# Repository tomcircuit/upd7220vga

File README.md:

# upd7220vga
VGA display using NEC uPD7220 Graphic Display Processor and MAX II CPLD

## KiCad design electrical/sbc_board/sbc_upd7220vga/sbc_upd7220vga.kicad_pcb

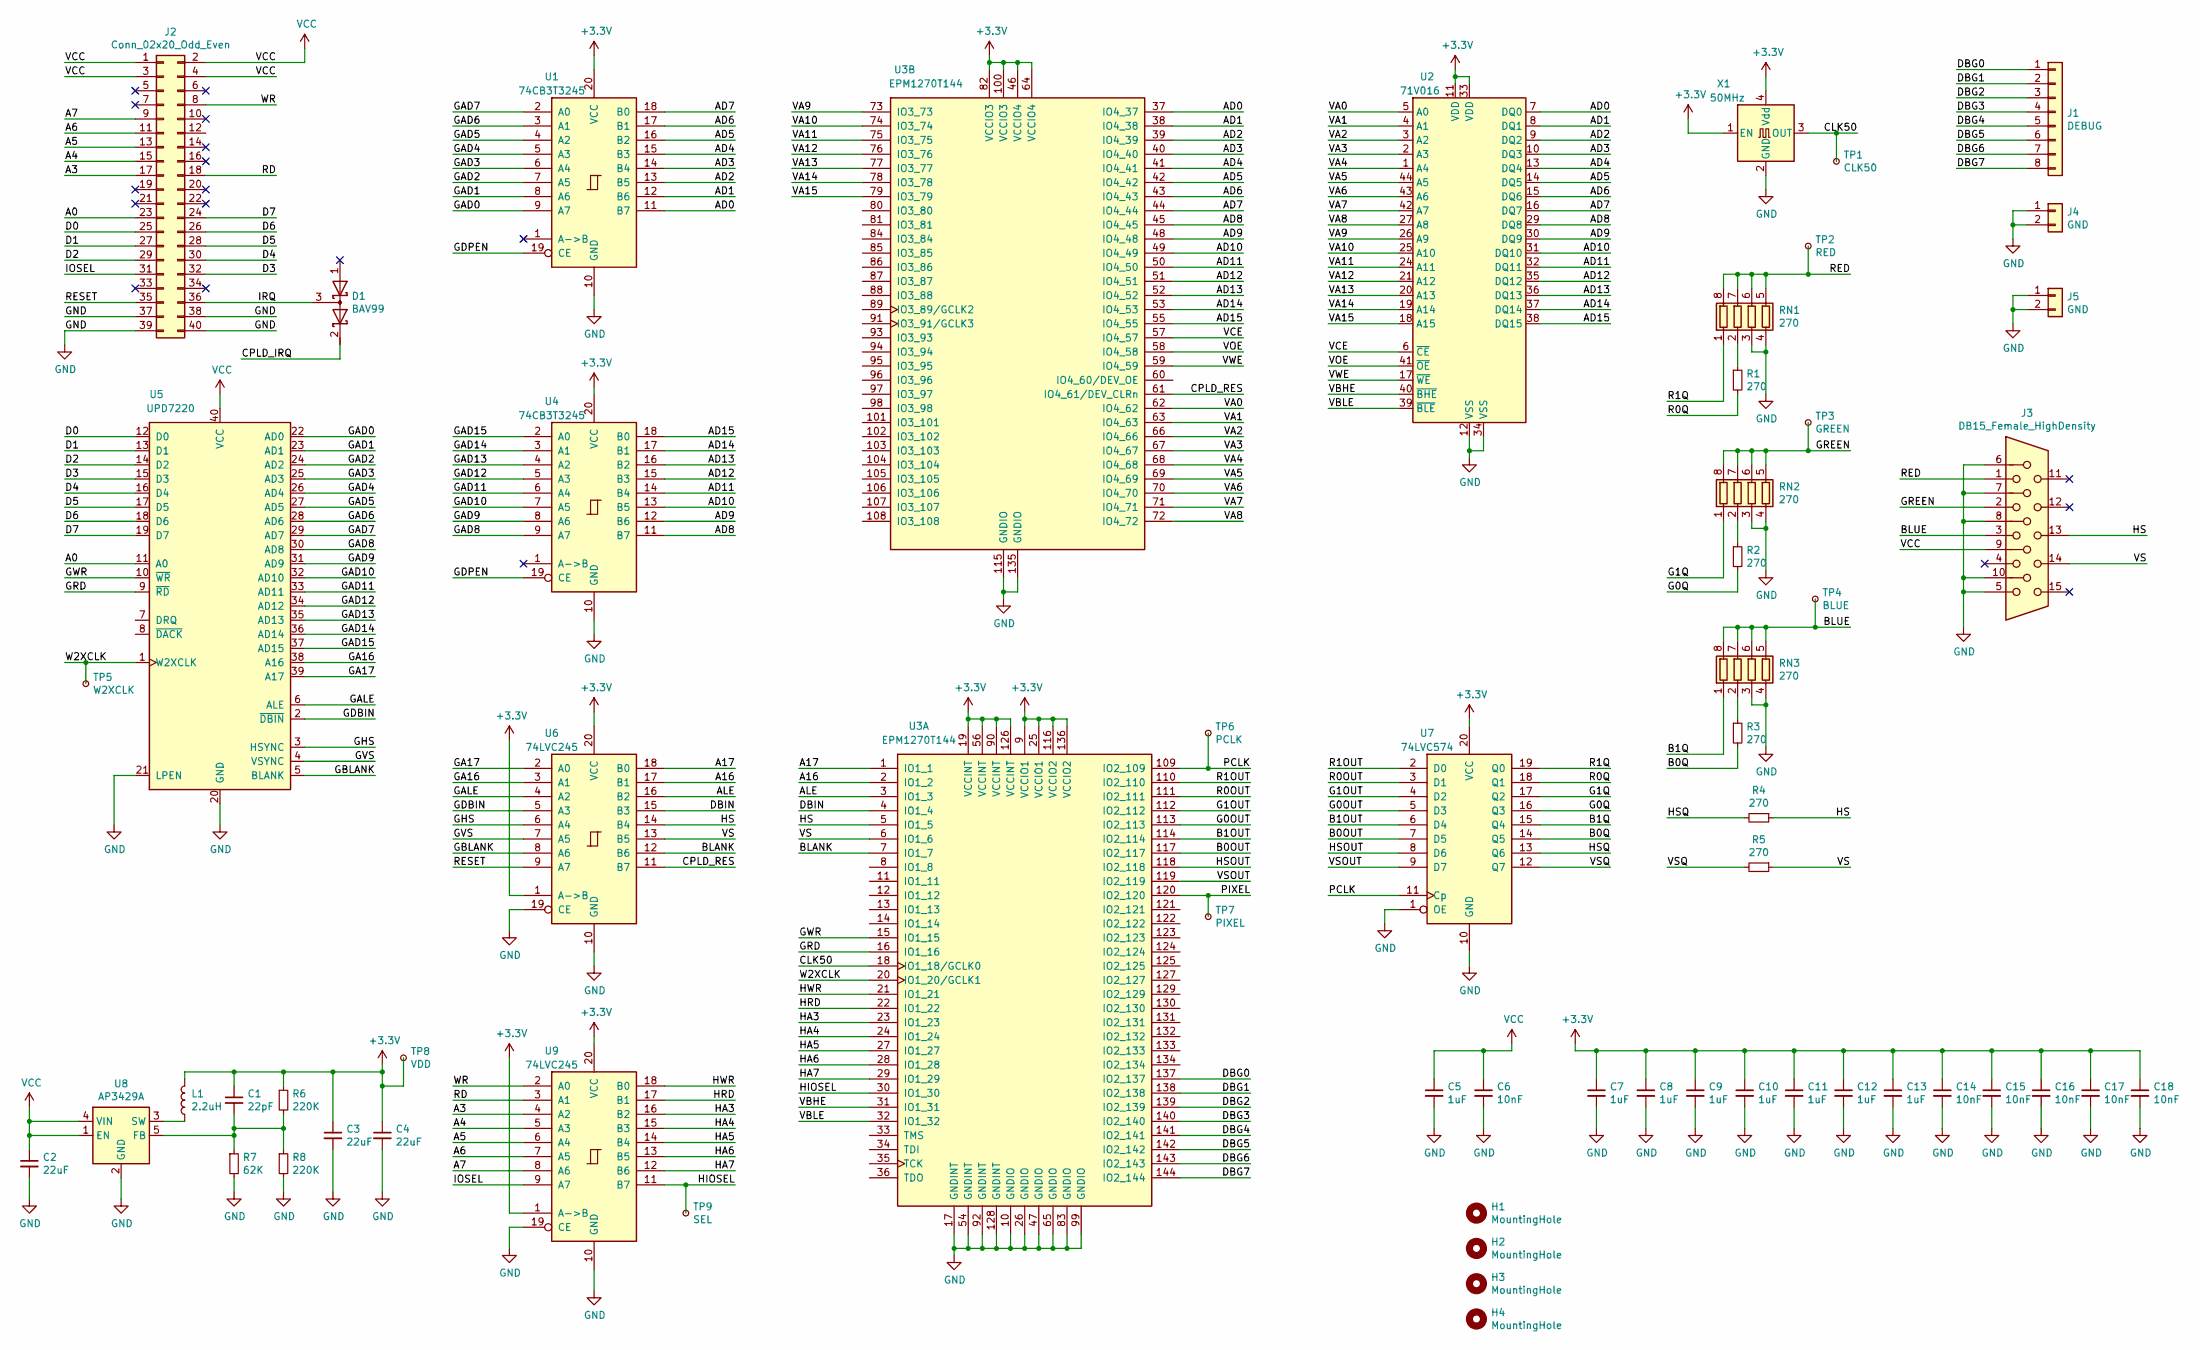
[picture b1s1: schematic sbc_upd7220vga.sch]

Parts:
C1: 22pF; C_0805_2012Metric_Pad1.18x1.45mm_HandSolder
C2, C3, C4: 22uF; C_0805_2012Metric_Pad1.18x1.45mm_HandSolder
C5, C7, C8, C9, C10, C11, C12, C13: 1uF; C_0805_2012Metric_Pad1.18x1.45mm_HandSolder
C6, C14, C15, C16, C17, C18: 10nF; C_0805_2012Metric_Pad1.18x1.45mm_HandSolder
D1: BAV99; SOT-23_Handsoldering
H1, H2, H3, H4: MountingHole; MountingHole_4.3mm_M4
J1: DEBUG; PinHeader_1x08_P2.54mm_Vertical
J2: Conn_02x20_Odd_Even; PinHeader_2x20_P2.54mm_Vertical
J3: DB15_Female_HighDensity; DSUB-15-HD_Female_Horizontal_P2.29x2.54mm_EdgePinOffset9.40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
J4, J5: GND; PinHeader_1x02_P2.54mm_Vertical
L1: 2.2uH; L_Taiyo-Yuden_NR-30xx_HandSoldering; MPN NRH3012T2R2MN
R1, R2, R3, R4, R5: 270; R_0805_2012Metric_Pad1.20x1.40mm_HandSolder
R6, R8: 220K; R_0805_2012Metric_Pad1.20x1.40mm_HandSolder
R7: 62K; R_0805_2012Metric_Pad1.20x1.40mm_HandSolder
RN1, RN2, RN3: 270; R_Array_Concave_4x0603
TP1: CLK50; TestPoint_Plated_Hole_D2.0mm
TP2: RED; TestPoint_Plated_Hole_D2.0mm
TP3: GREEN; TestPoint_Plated_Hole_D2.0mm
TP4: BLUE; TestPoint_Plated_Hole_D2.0mm
TP5: W2XCLK; TestPoint_Plated_Hole_D2.0mm
TP6: PCLK; TestPoint_Plated_Hole_D2.0mm
TP7: PIXEL; TestPoint_Plated_Hole_D2.0mm
TP8: VDD; TestPoint_Plated_Hole_D2.0mm
TP9: SEL; TestPoint_Plated_Hole_D2.0mm
U1, U4: 74CB3T3245; TSSOP-20_4.4x6.5mm_P0.65mm
U2: 71V016; TSOP-II-44_10.16x18.41mm_P0.8mm
U3: EPM1270T144; LQFP-144_20x20mm_P0.5mm
U5: UPD7220; DIP-40_W15.24mm
U6, U9: 74LVC245; TSSOP-20_4.4x6.5mm_P0.65mm
U7: 74LVC574; TSSOP-20_4.4x6.5mm_P0.65mm
U8: AP3429A; SOT-23-5
X1: 50MHz; Oscillator_SMD_Abracon_ASV-4Pin_7.0x5.1mm

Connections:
+3V3: C1.1, C3.1, C4.1, C7.1, C8.1, C9.1, C10.1, C11.1, C12.1, C13.1, C14.1, C15.1, C16.1, C17.1, C18.1, L1.2, R6.1, TP8.1, U1.20 (VCC), U2.11 (VDD), U2.33 (VDD), U3.9 (VCCIO1), U3.19 (VCCINT), U3.25 (VCCIO1), U3.46 (VCCIO4), U3.56 (VCCINT), U3.64 (VCCIO4), U3.82 (VCCIO3), U3.90 (VCCINT), U3.100 (VCCIO3), U3.116 (VCCIO2), U3.126 (VCCINT), U3.136 (VCCIO2), U4.20 (VCC), U6.1 (A->B), U6.20 (VCC), U7.20 (VCC), U9.1 (A->B), U9.20 (VCC), X1.1 (EN), X1.4 (Vdd)
/A0: J2.23, U5.11 (A0)
/A3: J2.17, U9.4 (A2)
/A4: J2.15, U9.5 (A3)
/A5: J2.13, U9.6 (A4)
/A6: J2.11, U9.7 (A5)
/A7: J2.9, U9.8 (A6)
/A16: U3.2 (IO1_2), U6.17 (B1)
/A17: U3.1 (IO1_1), U6.18 (B0)
/AD0: U1.11 (B7), U2.7 (DQ0), U3.37 (IO4_37)
/AD1: U1.12 (B6), U2.8 (DQ1), U3.38 (IO4_38)
/AD2: U1.13 (B5), U2.9 (DQ2), U3.39 (IO4_39)
/AD3: U1.14 (B4), U2.10 (DQ3), U3.40 (IO4_40)
/AD4: U1.15 (B3), U2.13 (DQ4), U3.41 (IO4_41)
/AD5: U1.16 (B2), U2.14 (DQ5), U3.42 (IO4_42)
/AD6: U1.17 (B1), U2.15 (DQ6), U3.43 (IO4_43)
/AD7: U1.18 (B0), U2.16 (DQ7), U3.44 (IO4_44)
/AD8: U2.29 (DQ8), U3.45 (IO4_45), U4.11 (B7)
/AD9: U2.30 (DQ9), U3.48 (IO4_48), U4.12 (B6)
/AD10: U2.31 (DQ10), U3.49 (IO4_49), U4.13 (B5)
/AD11: U2.32 (DQ11), U3.50 (IO4_50), U4.14 (B4)
/AD12: U2.35 (DQ12), U3.51 (IO4_51), U4.15 (B3)
/AD13: U2.36 (DQ13), U3.52 (IO4_52), U4.16 (B2)
/AD14: U2.37 (DQ14), U3.53 (IO4_53), U4.17 (B1)
/AD15: U2.38 (DQ15), U3.55 (IO4_55), U4.18 (B0)
/ALE: U3.3 (IO1_3), U6.16 (B2)
/B0OUT: U3.117 (IO2_117), U7.7 (D5)
/B0Q: R3.2, U7.14 (Q5)
/B1OUT: U3.114 (IO2_114), U7.6 (D4)
/B1Q: RN3.1 (R1.1), U7.15 (Q4)
/BLANK: U3.7 (IO1_7), U6.12 (B6)
/BLUE: J3.3, RN3.5 (R4.2), RN3.6 (R3.2), RN3.7 (R2.2), RN3.8 (R1.2), TP4.1
/CLK50: TP1.1, U3.18 (IO1_18/GCLK0), X1.3 (OUT)
/CPLD_RES: U3.61 (IO4_61/DEV_CLRn), U6.11 (B7)
/D0: J2.25, U5.12 (D0)
/D1: J2.27, U5.13 (D1)
/D2: J2.29, U5.14 (D2)
/D3: J2.32, U5.15 (D3)
/D4: J2.30, U5.16 (D4)
/D5: J2.28, U5.17 (D5)
/D6: J2.26, U5.18 (D6)
/D7: J2.24, U5.19 (D7)
/DBG0: J1.1, U3.137 (IO2_137)
/DBG1: J1.2, U3.138 (IO2_138)
/DBG2: J1.3, U3.139 (IO2_139)
/DBG3: J1.4, U3.140 (IO2_140)
/DBG4: J1.5, U3.141 (IO2_141)
/DBG5: J1.6, U3.142 (IO2_142)
/DBG6: J1.7, U3.143 (IO2_143)
/DBG7: J1.8, U3.144 (IO2_144)
/DBIN: U3.4 (IO1_4), U6.15 (B3)
/G0OUT: U3.113 (IO2_113), U7.5 (D3)
/G0Q: R2.2, U7.16 (Q3)
/G1OUT: U3.112 (IO2_112), U7.4 (D2)
/G1Q: RN2.1 (R1.1), U7.17 (Q2)
/GA16: U5.38 (A16), U6.3 (A1)
/GA17: U5.39 (A17), U6.2 (A0)
/GAD0: U1.9 (A7), U5.22 (AD0)
/GAD1: U1.8 (A6), U5.23 (AD1)
/GAD2: U1.7 (A5), U5.24 (AD2)
/GAD3: U1.6 (A4), U5.25 (AD3)
/GAD4: U1.5 (A3), U5.26 (AD4)
/GAD5: U1.4 (A2), U5.27 (AD5)
/GAD6: U1.3 (A1), U5.28 (AD6)
/GAD7: U1.2 (A0), U5.29 (AD7)
/GAD8: U4.9 (A7), U5.30 (AD8)
/GAD9: U4.8 (A6), U5.31 (AD9)
/GAD10: U4.7 (A5), U5.32 (AD10)
/GAD11: U4.6 (A4), U5.33 (AD11)
/GAD12: U4.5 (A3), U5.34 (AD12)
/GAD13: U4.4 (A2), U5.35 (AD13)
/GAD14: U4.3 (A1), U5.36 (AD14)
/GAD15: U4.2 (A0), U5.37 (AD15)
/GALE: U5.6 (ALE), U6.4 (A2)
/GBLANK: U5.5 (BLANK), U6.8 (A6)
/GDBIN: U5.2 (~DBIN), U6.5 (A3)
/GDPEN: U1.19 (CE), U4.19 (CE)
/GHS: U5.3 (HSYNC), U6.6 (A4)
/GRD: U3.16 (IO1_16), U5.9 (~RD)
/GREEN: J3.2, RN2.5 (R4.2), RN2.6 (R3.2), RN2.7 (R2.2), RN2.8 (R1.2), TP3.1
/GVS: U5.4 (VSYNC), U6.7 (A5)
/GWR: U3.15 (IO1_15), U5.10 (~WR)
/HA3: U3.23 (IO1_23), U9.16 (B2)
/HA4: U3.24 (IO1_24), U9.15 (B3)
/HA5: U3.27 (IO1_27), U9.14 (B4)
/HA6: U3.28 (IO1_28), U9.13 (B5)
/HA7: U3.29 (IO1_29), U9.12 (B6)
/HIOSEL: TP9.1, U3.30 (IO1_30), U9.11 (B7)
/HRD: U3.22 (IO1_22), U9.17 (B1)
/HS: J3.13, R4.1, U3.5 (IO1_5), U6.14 (B4)
/HSOUT: U3.118 (IO2_118), U7.8 (D6)
/HSQ: R4.2, U7.13 (Q6)
/HWR: U3.21 (IO1_21), U9.18 (B0)
/IOSEL: J2.31, U9.9 (A7)
/IRQ: D1.3 (common), J2.36
/PCLK: TP6.1, U3.109 (IO2_109), U7.11 (Cp)
/PIXEL: TP7.1, U3.120 (IO2_120)
/R0OUT: U3.111 (IO2_111), U7.3 (D1)
/R0Q: R1.2, U7.18 (Q1)
/R1OUT: U3.110 (IO2_110), U7.2 (D0)
/R1Q: RN1.1 (R1.1), U7.19 (Q0)
/RD: J2.18, U9.3 (A1)
/RED: J3.1, RN1.5 (R4.2), RN1.6 (R3.2), RN1.7 (R2.2), RN1.8 (R1.2), TP2.1
/RESET: J2.35, U6.9 (A7)
/VA0: U2.5 (A0), U3.62 (IO4_62)
/VA1: U2.4 (A1), U3.63 (IO4_63)
/VA2: U2.3 (A2), U3.66 (IO4_66)
/VA3: U2.2 (A3), U3.67 (IO4_67)
/VA4: U2.1 (A4), U3.68 (IO4_68)
/VA5: U2.44 (A5), U3.69 (IO4_69)
/VA6: U2.43 (A6), U3.70 (IO4_70)
/VA7: U2.42 (A7), U3.71 (IO4_71)
/VA8: U2.27 (A8), U3.72 (IO4_72)
/VA9: U2.26 (A9), U3.73 (IO3_73)
/VA10: U2.25 (A10), U3.74 (IO3_74)
/VA11: U2.24 (A11), U3.75 (IO3_75)
/VA12: U2.21 (A12), U3.76 (IO3_76)
/VA13: U2.20 (A13), U3.77 (IO3_77)
/VA14: U2.19 (A14), U3.78 (IO3_78)
/VA15: U2.18 (A15), U3.79 (IO3_79)
/VBHE: U2.40 (~BHE), U3.31 (IO1_31)
/VBLE: U2.39 (~BLE), U3.32 (IO1_32)
/VCE: U2.6 (~CE), U3.57 (IO4_57)
/VOE: U2.41 (~OE), U3.58 (IO4_58)
/VS: J3.14, R5.1, U3.6 (IO1_6), U6.13 (B5)
/VSOUT: U3.119 (IO2_119), U7.9 (D7)
/VSQ: R5.2, U7.12 (Q7)
/VWE: U2.17 (~WE), U3.59 (IO4_59)
/W2XCLK: TP5.1, U3.20 (IO1_20/GCLK1), U5.1 (W2XCLK)
/WR: J2.8, U9.2 (A0)
GND: C2.2, C3.2, C4.2, C5.2, C6.2, C7.2, C8.2, C9.2, C10.2, C11.2, C12.2, C13.2, C14.2, C15.2, C16.2, C17.2, C18.2, J2.37, J2.38, J2.39, J2.40, J3.5, J3.6, J3.7, J3.8, J3.10, J4.1, J4.2, J5.1, J5.2, R7.2, R8.2, RN1.3 (R3.1), RN1.4 (R4.1), RN2.3 (R3.1), RN2.4 (R4.1), RN3.3 (R3.1), RN3.4 (R4.1), U1.10 (GND), U2.12 (VSS), U2.34 (VSS), U3.10 (GNDIO), U3.17 (GNDINT), U3.26 (GNDIO), U3.47 (GNDIO), U3.54 (GNDINT), U3.65 (GNDIO), U3.83 (GNDIO), U3.92 (GNDINT), U3.99 (GNDIO), U3.115 (GNDIO), U3.128 (GNDINT), U3.135 (GNDIO), U4.10 (GND), U5.20 (GND), U5.21 (LPEN), U6.10 (GND), U6.19 (CE), U7.1 (OE), U7.10 (GND), U8.2 (GND), U9.10 (GND), U9.19 (CE), X1.2 (GND)
unnamed: C1.2, R6.2, R7.1, R8.1, U8.5 (FB)
unnamed: L1.1, U8.3 (SW)
unnamed: R1.1, RN1.2 (R2.1)
unnamed: R2.1, RN2.2 (R2.1)
unnamed: R3.1, RN3.2 (R2.1)
VCC: C2.1, C5.1, C6.1, J2.1, J2.2, J2.3, J2.4, J3.9, U5.40 (VCC), U8.1 (EN), U8.4 (VIN)

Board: 2 copper layers, 59 parts (0 on the bottom side), 137 nets, no tracks yet.

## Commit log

2021-02-07 bring initial files into GitHub
    Bringing work-in-progress into GitHub.
2021-02-08 VHDL update
    optimized fall processing, updated toplevel, updated FSM to include SRAM CS (power consumption)
2021-02-10 more VHDL tuning
    implemented pixel shift register. added sync pipe delay path. cleaned up signal names to be more consistent.
2021-02-10 updated toplevel and restored registers
2021-02-11 started KiCAD project
    started kicad project for SBC PCB
2021-02-11 Kicad schematic capture
    still need JTAG for CPLD but otherwise I think it's complete. PCB netlist load passes.
